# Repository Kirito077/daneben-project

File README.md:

# Daneben! — Smart Waste Bin Detection System

**Course:** Mikro-controller (5. Semester) · Hochschule Niederrhein (HSNR)  
**Antigravity Project:** `daneben-project` (`C:\Users\ekwug\.gemini\antigravity\projects\daneben-project`)  
**Workspace:** `C:\Users\ekwug\OneDrive\Documents\Deutschland\HSNR\Studium\5.Semester\Mikro-contoller\Daneben Projekt`  

---

## 📌 Project Overview
"Daneben!" is a solar-powered, retrofittable IoT Edge AI system mounted on municipal waste bins. It monitors the surrounding pavement for illegally dumped waste (bags, boxes), ignores pedestrians to preserve privacy (GDPR compliance), prompts users with acoustic messages if space remains inside the container, and reports fill/dumping status live to sanitation departments via MQTT / LoRaWAN.

---

## 📂 Repository Structure

* 📁 **`docs/`**
  * **Presentations & Pitches (1-Minute Sales Pitch & Condensed Editions):**
    * [`Daneben_Condensed_Pitch_Visual_DE_AutoNarrated_1Min.pptx`](docs/Daneben_Condensed_Pitch_Visual_DE_AutoNarrated_1Min.pptx) — **Auto-Narrated 6-Slide Pitch (Visual Edition, 54s Total)**: Fully autonomous presentation with embedded studio-quality German neural voice narration (`de-DE-KillianNeural`). When started (**F5**), it speaks the entire presentation out loud and auto-advances through all 6 slides in **exactly 54 seconds** (strictly inside 1 minute) without touching the keyboard or mouse.
    * [`Daneben_Condensed_Pitch_DE_AutoNarrated_1Min.pptx`](docs/Daneben_Condensed_Pitch_DE_AutoNarrated_1Min.pptx) — **Auto-Narrated 6-Slide Pitch (Standard Edition, 54s Total)**: Standard analytical edition with identical embedded auto-narration and 54-second automatic slide timings.
    * [`Daneben_Condensed_Pitch_Visual_DE.pptx`](docs/Daneben_Condensed_Pitch_Visual_DE.pptx) ([🇬🇧 EN Version](docs/Daneben_Condensed_Pitch_Visual_EN.pptx)) — **Condensed 6-Slide Pitch (Visual Doodle Edition)**: Streamlined 6-slide deck combining Problem 1 (side-dumping) & Problem 2 (blind fleet routes) side-by-side with vector doodles and stat callouts, omitting the CCTV/market gap slide, preserving the exploded 3D CAD production hardware architecture with native editable callouts, omitting the Geschäftsmodell, and concluding with the "Let's keep the city clean!" wrap-up slide.
    * [`Daneben_Condensed_Pitch_DE.pptx`](docs/Daneben_Condensed_Pitch_DE.pptx) ([🇬🇧 EN Version](docs/Daneben_Condensed_Pitch_EN.pptx)) — **Condensed 6-Slide Pitch (Standard Edition)**: Clean analytical 6-slide presentation with structured cards, exploded CAD hardware, municipal ROI, and closing mission slide.
    * [`Daneben_1Min_Sales_Pitch_Visual_Edition.pptx`](docs/Daneben_1Min_Sales_Pitch_Visual_Edition.pptx) ([🇩🇪 DE Version](docs/Daneben_1Min_Sales_Pitch_Visual_Edition_DE.pptx)) — **Visual Doodle Edition (Full Pitch - 9 Slides)**: Complete 9-slide pitch with animated vector illustrations, exploded 3D CAD hardware, business model, and closing slogan.
    * [`Daneben_Pitch_Visual_Edition_DE_ohne_Geschaeftsmodell.pptx`](docs/Daneben_Pitch_Visual_Edition_DE_ohne_Geschaeftsmodell.pptx) ([🇬🇧 EN Version](docs/Daneben_Pitch_Visual_Edition_EN_no_business_model.pptx)) — **Academic Edition (Ohne Hardware & Geschäftsmodell - 7 Slides)**: Streamlined 7-slide version omitting both the exploded hardware and business model slides.
    * [`Daneben_1Min_Sales_Pitch.pptx`](docs/Daneben_1Min_Sales_Pitch.pptx) ([🇩🇪 DE Version](docs/Daneben_1Min_Sales_Pitch_DE.pptx)) — **Standard Edition (Full Pitch - 9 Slides)**: Clean white 9-slide presentation with side-by-side analytical cards, labeled exploded hardware, business model, and timed speaker notes.
    * [`Daneben_Pitch_DE_ohne_Geschaeftsmodell.pptx`](docs/Daneben_Pitch_DE_ohne_Geschaeftsmodell.pptx) ([🇬🇧 EN Version](docs/Daneben_Pitch_EN_no_business_model.pptx)) — **Standard Technical Edition (Ohne Hardware & Geschäftsmodell - 7 Slides)**: 7-slide standard presentation without exploded hardware or startup business case.
    * [`Daneben_1Min_Pitch_Script_EN.pdf`](docs/Daneben_1Min_Pitch_Script_EN.pdf) ([🇩🇪 DE Version](docs/Daneben_1Min_Pitch_Script_DE.pdf)) — **Spoken Pitch Scripts**: Precise 60-second word-for-word presentation delivery script with timed stage directions (0–15s Hook, 15–30s Problem, 30–45s Solution, 45–60s CTA).
  * **Bill of Materials (BOM) — Official Production Specifications:**
    * [`Daneben_Hardware_BoM_Full.pdf`](docs/Daneben_Hardware_BoM_Full.pdf) ([📊 Excel .xlsx](docs/Daneben_Hardware_BoM_Full.xlsx)) — **Full System BOM**: Complete 13-item production specification (compute, dual sensors, audio amp, speaker, solar MPPT, Li-ion cell, Carrier Board v2 PCB, calibration & interface hardware kit, optical window, membrane vents) in clean Excel grid layout (€70.77 gross parts total).
    * [`Daneben_Hardware_BoM_Prototype.pdf`](docs/Daneben_Hardware_BoM_Prototype.pdf) ([📊 Excel .xlsx](docs/Daneben_Hardware_BoM_Prototype.xlsx)) — **Benchtop Prototype BOM**: Focused 11-item BOM containing only the core electronics and Carrier Board v2.0 electrical components (ESP32-S3 Sense, dual ultrasonic sensors, I2S amp, speaker, custom carrier PCB, 2× tactile calibration buttons, 3× status LEDs, SPDT power switch, USB-C 5V power input, screw terminals, socket headers; mechanical fasteners excluded) (€40.75 gross parts total).
    * [`Daneben_Hardware_BoM_Core.pdf`](docs/Daneben_Hardware_BoM_Core.pdf) ([📊 Excel .xlsx](docs/Daneben_Hardware_BoM_Core.xlsx)) — **Core Electronics BOM**: Focused specification for the 4 primary electronic subsystems (ESP32-S3 Sense, 2× JSN-SR04T waterproof ultrasonic, MAX98357A I2S amp, 3W speaker) with Farnell & Funduino primary vendor sourcing (€33.25 gross parts total).
    * 📁 [`docs/archive/legacy_boms/`](docs/archive/legacy_boms/) — Archived legacy HTML and duplicate BOM iterations.
  * **Visual Architecture & Mindmaps:**
    * [`Daneben_Operational_Flowchart.pdf`](docs/Daneben_Operational_Flowchart.pdf) & [`.html`](docs/Daneben_Operational_Flowchart.html) — Complete operational flowchart mapping every state to its hardware component and software functionality.
    * [`Daneben_Project_Mindmap.pdf`](docs/Daneben_Project_Mindmap.pdf) & [`.html`](docs/Daneben_Project_Mindmap.html) — Presentation-ready visual Mind Map (Landscape PDF & interactive dashboard).
    * [`Project_Mindmap.md`](docs/Project_Mindmap.md) — Raw Markdown/Mermaid Mind Map chart.
  * **Technical Reports & Blueprints:**
    * [`Enclosure_3D_Design_Report_Detailed.pdf`](docs/Enclosure_3D_Design_Report_Detailed.pdf) — 2D Orthographic Blueprint (Front, Side, Top views) with exact millimeter dimensions, waterproofing details, and exploded 3D renders.
    * [`Enclosure_3D_Design_Report.pdf`](docs/Enclosure_3D_Design_Report.pdf) — Conceptual 3D external and exploded visualizations.
  * **Engineering Documentation & Analysis:**
    * [`CONVERSATION_HISTORY.md`](docs/CONVERSATION_HISTORY.md) — Complete transcript and architectural evolution of all discussions, trade-offs (RoboDog vs. Daneben), and engineering decisions.
    * [`Project_Workflow_and_Market_Analysis.md`](docs/Project_Workflow_and_Market_Analysis.md) — Problem statement, market analysis (municipalities, smart cities, housing), SaaS revenue model, and 5-year lifespan calculation.
    * [`AI_and_System_Expansions.md`](docs/AI_and_System_Expansions.md) — Comparison between pixel-differencing and Edge AI (Edge Impulse), internal container capacity sensing, and smart fleet telemetry.
* 📁 **`hardware/`**
  * [`daneben_enclosure.scad`](hardware/daneben_enclosure.scad) — Parametric 3D CAD model for OpenSCAD.
  * [`daneben_enclosure.stl`](hardware/daneben_enclosure.stl) — Compiled 3D mesh model ready to open directly in **Autodesk Inventor** or Windows 3D Viewer.
  * [`Enclosure_and_Hardware.md`](hardware/Enclosure_and_Hardware.md) — IP67 sealing strategy, 20° sloped roof, drip edges, and isolated battery cartridge system.
  * [`Parts_List.md`](hardware/Parts_List.md) — Technical Bill of Materials (BOM) with unit costs at scale (~$29.50 BOM).
  * [`Procurement_Parts_List.md`](hardware/Procurement_Parts_List.md) — Complete purchasing list with **exact dimensions, specs, and 3 fast-shipping store links** per component (Amazon.de, BerryBase, Reichelt).
  * [`Budget_Showcase_Prototype_Template.md`](hardware/Budget_Showcase_Prototype_Template.md) — Low-cost (~€28) tabletop demonstration template for student presentations and live demo evaluations.
  * 📁 **[`Daneben_Prototype_Carrier_Board/`](hardware/Daneben_Prototype_Carrier_Board/)** — Complete KiCad 9 modular prototype carrier board project (`.kicad_pcb`, `.kicad_sch`, `.kicad_pro`, PDF/SVG exports, and generator scripts) with integrated power rails, sensor sockets, audio header, and modular expansion buses.
  * 📁 **`Daneben circuit board/`** — Original KiCad project files (`.kicad_pcb`, `.kicad_sch`, `.kicad_pro`) implementing the power management, ESP32-S3 processing, and sensor interfaces.
* 📁 **`src/`**
  * [`main.cpp`](src/main.cpp) — ESP32-S3 firmware: 2-stage distance debounce filter (8-second timer), Edge Impulse camera inference, and MQTT publishing.
  * [`internal_sensor.cpp`](src/internal_sensor.cpp) — Internal container fill level telematics (stationary upper collar angled mount, 0–100% continuous tracking with trigonometric depth correction) and MAX98357A I2S acoustic deterrent logic.
  * [`calibration.h`](src/calibration.h) — Dual tactile button calibration engine: interactive baseline zeroing, threshold configuration, EEPROM/NVS persistent storage, and status LED telemetry.

---

## ⚡ Quick Technical Specifications
* **MCU:** ESP32-S3 Sense (Dual-Core 240MHz, 8MB PSRAM, Wi-Fi / BLE, Camera interface).
* **Presence Sensor:** Multi-zone ToF (VL53L5CX) or JSN-SR04T Waterproof Ultrasonic (angled 45° at pavement).
* **Internal Sensor:** JSN-SR04T Waterproof Ultrasonic transducer mounted on the fixed upper collar/inner rim angled downward (~25°) toward the central trash cone (eliminates moving wires across swinging lids, prevents snagging during municipal emptying, and delivers continuous 0–100% capacity tracking).
* **Power:** 2&times; 18650 LiFePO4 cells (3.2V nominal, 3000mAh) + 5V 1.5W Monocrystalline solar panel + CN3791 MPPT charger.
* **Enclosure Rating:** IP67 (Polycarbonate, 20° sloped roof, drip edge, silicone O-rings, borosilicate optical glass with UV adhesive, hydrophobic ePTFE acoustic membrane for speaker).

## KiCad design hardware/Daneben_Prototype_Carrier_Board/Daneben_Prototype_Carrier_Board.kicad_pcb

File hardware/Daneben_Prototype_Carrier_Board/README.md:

# "Daneben!" — Modular Prototype Carrier Board Version 2.0 (KiCad 9)

> **Purpose:** Custom modular carrier board designed to house all electronic subsystems of the "Daneben!" system for student showcases, laboratory testing, and benchtop demonstration without messy floating wires.  
> **Course / Academic Context:** Hochschule Niederrhein (HSNR) · 5. Semester · Mikro-controller  
> **KiCad Version:** 9.0.4  
> **Dimensions:** 130.0 mm &times; 90.0 mm (FR4 2-Layer, 1.6 mm thickness, 4&times; M3 mounting holes, R=4.0 mm rounded corners)  
> **Active Production Version:** Version 2.0 (Historical V1 files archived in [`archive_v1/`](file:///c:/Users/ekwug/OneDrive/Documents/Deutschland/HSNR/Studium/5.Semester/Mikro-contoller/Daneben%20Projekt/hardware/Daneben_Prototype_Carrier_Board/archive_v1/))

---

## 1. Subsystem Architecture & Features (v2.0)

This board acts as a central modular motherboard, providing standardized sockets, mechanical standoff mounts, dedicated power conditioning, and hardware calibration controls:

```
+-----------------------------------------------------------------------------------------------------------------------+
| [H1: M3]                                                                                                     [H2: M3] |
|                                                                                                                       |
|  +---------------------------------------+      +-------------------------------+      +----------------------------+ |
|  |     AJ-SR04M DOCK 1 (OUTSIDE / FLOOR) |      |      SEEED XIAO ESP32-S3      |      |     I2S AUDIO & SPEAKER    | |
|  |                                       |      |             SENSE             |      |                            | |
|  | [Transducer Jack Exits Left <---]     |      |                               |      | [J_AMP: MAX98357A Socket]  | |
|  |                                       |      |  [J_MCU_L]         [J_MCU_R]  |      |  (2x M2.5 Standoff Holes)  | |
|  | [4x M2.5 Standoff Mounting Holes]     |      |  D0: TRIG_OUT      D7: IN_STAT|      |                            | |
|  | [J_AJ_OUT: 4-Pin Socket (5V/Trig/Echo/GND)]  |  D1: ECHO_OUT      D8: BCLK   |      | [J_SPK: 2-Pin Screw Term]  | |
|  +---------------------------------------+      |  D2: TRIG_IN       D9: LRC    |      |  (SPK+ / SPK- Differential)| |
|                                                 |  D3: ECHO_IN       D10: DIN   |      +----------------------------+ |
|                                                 |  D4: BTN_CAL_OUT   3V3: +3V3  |                                     |
|  +---------------------------------------+      |  D5: BTN_CAL_IN    GND: GND   |      +----------------------------+ |
|  |     AJ-SR04M DOCK 2 (INSIDE / DEPTH)  |      |  D6: OUT_STAT      5V: +5V    |      |     SIZABLE CALIBRATION    | |
|  |                                       |      +-------------------------------+      |     CONTROLS (12x12mm)     | |
|  | [Transducer Jack Exits Left <---]     |                                             |                            | |
|  |                                       |      +-------------------------------+      | [SW_CAL_OUT: 12x12mm Blue] | |
|  | [4x M2.5 Standoff Mounting Holes]     |      |   DEDICATED USB-C POWER ENTRY |      |  (Floor Distance Reference)| |
|  | [J_AJ_IN: 4-Pin Socket (5V/Trig/Echo/GND)]   |                               |      | [LED_CAL_OUT: Blue Status] | |
|  +---------------------------------------+      | [J_USBC: Type-C Port (5V)]    |      |                            | |
|                                                 | [R_CC1 / R_CC2: 5.1k PD]      |      | [SW_CAL_IN: 12x12mm Amber] | |
|                                                 | [SW_PWR: On/Off Slide Switch] |      |  (Bin Depth 1m-4m NVS Cal) | |
|                                                 | [C_BULK1: 100uF Bulk Reservoir]      | [LED_CAL_IN: Amber Status] | |
|                                                 | [J_EXT_5V: Screw Terminal In] |      +----------------------------+ |
|                                                 | [LED_PWR: Green Power LED]    |                                     |
|                                                 +-------------------------------+      [J_AUX: 1x6 Expansion Header]  |
| [H3: M3]                                                                                                     [H4: M3] |
+-----------------------------------------------------------------------------------------------------------------------+
```

---

## 2. Key Engineering Improvements in v2.0

### 2.1 Zero-Friction AJ-SR04M Waterproof Transducer Docks
* **Mechanical Stability:** Each AJ-SR04M sensor board is fastened to the carrier board using **4&times; M2.5 standoff screws**, eliminating wiggling, loose contacts, and vibrations.
* **Cable Clearance:** Both modules have their cylindrical metal transducer connectors positioned directly along the left PCB edge, pointing into free air. When the thick shielded transducer cables are attached, they exit outward with **zero bending friction or mechanical obstruction**.

### 2.2 Dedicated Onboard USB-C Power Entry
* Standard USB Type-C receptacle (`J_USBC`) on the bottom board edge with two 5.1 kΩ pull-down resistors (`R_CC1`, `R_CC2`) on CC1 and CC2. Automatically negotiates clean 5V (up to 3A) from modern USB-PD power banks and phone chargers.
* Onboard slide switch (`SW_PWR`) and green power LED (`LED_PWR`).
* 100 µF bulk capacitor (`C_BULK1`) buffers the sudden current draws of the MAX98357A Class-D amplifier.

### 2.3 Sizable 12&times;12 mm Dual Calibration Pushbuttons
* Whisbins and municipal waste bins vary widely in geometry (standard 120L/240L bins are ~1.0m deep, whereas large commercial or underground containers can be 2.0m to 4.0m deep).
* **`SW_CAL_OUT` (Outside / Floor Reference):** Runs 15 ultrasonic pings, averages baseline floor distance, and persists it into non-volatile storage (`Preferences` / NVS).
* **`SW_CAL_IN` (Inside / Bin Depth Reference):** One-click empty-bin calibration that auto-scales full percentage (0–100%) dynamically for any container depth.
* Driven by [`src/calibration.h`](file:///c:/Users/ekwug/OneDrive/Documents/Deutschland/HSNR/Studium/5.Semester/Mikro-contoller/Daneben%20Projekt/src/calibration.h).

---

## 3. How to View in KiCad 3D Viewer

1. Open [`Daneben_Prototype_Carrier_Board.kicad_pro`](file:///c:/Users/ekwug/OneDrive/Documents/Deutschland/HSNR/Studium/5.Semester/Mikro-contoller/Daneben%20Projekt/hardware/Daneben_Prototype_Carrier_Board/Daneben_Prototype_Carrier_Board.kicad_pro) in KiCad.
2. Open the PCB Editor (`Daneben_Prototype_Carrier_Board.kicad_pcb`).
3. Press **`Alt + 3`** (or go to **View &rarr; 3D Viewer**).
4. Real-time 3D models will display with exact millimeter alignment for the AJ-SR04M modules, Seeed XIAO Sense, MAX98357A, USB-C jack, and 12x12mm switches.

---

## 4. File Manifest

### Active Production Files (Version 2.0):
* [`Daneben_Prototype_Carrier_Board.kicad_pro`](file:///c:/Users/ekwug/OneDrive/Documents/Deutschland/HSNR/Studium/5.Semester/Mikro-contoller/Daneben%20Projekt/hardware/Daneben_Prototype_Carrier_Board/Daneben_Prototype_Carrier_Board.kicad_pro): Main project.
* [`Daneben_Prototype_Carrier_Board.kicad_sch`](file:///c:/Users/ekwug/OneDrive/Documents/Deutschland/HSNR/Studium/5.Semester/Mikro-contoller/Daneben%20Projekt/hardware/Daneben_Prototype_Carrier_Board/Daneben_Prototype_Carrier_Board.kicad_sch): Full master schematic.
* [`Daneben_Prototype_Carrier_Board.kicad_pcb`](file:///c:/Users/ekwug/OneDrive/Documents/Deutschland/HSNR/Studium/5.Semester/Mikro-contoller/Daneben%20Projekt/hardware/Daneben_Prototype_Carrier_Board/Daneben_Prototype_Carrier_Board.kicad_pcb): Complete routed 130x90mm PCB.
* [`carrier_board_schematic.pdf`](file:///c:/Users/ekwug/OneDrive/Documents/Deutschland/HSNR/Studium/5.Semester/Mikro-contoller/Daneben%20Projekt/hardware/Daneben_Prototype_Carrier_Board/carrier_board_schematic.pdf): Master schematic PDF.
* [`carrier_board_pcb_layout.pdf`](file:///c:/Users/ekwug/OneDrive/Documents/Deutschland/HSNR/Studium/5.Semester/Mikro-contoller/Daneben%20Projekt/hardware/Daneben_Prototype_Carrier_Board/carrier_board_pcb_layout.pdf): PCB fabrication layout PDF.
* [`carrier_board_v2_3d_isometric.png`](file:///c:/Users/ekwug/OneDrive/Documents/Deutschland/HSNR/Studium/5.Semester/Mikro-contoller/Daneben%20Projekt/hardware/Daneben_Prototype_Carrier_Board/carrier_board_v2_3d_isometric.png): High-res 3D isometric render.
* [`carrier_board_v2_3d_top.png`](file:///c:/Users/ekwug/OneDrive/Documents/Deutschland/HSNR/Studium/5.Semester/Mikro-contoller/Daneben%20Projekt/hardware/Daneben_Prototype_Carrier_Board/carrier_board_v2_3d_top.png): High-res 3D top-down render.
* [`carrier_board_v2_3d_front_angle.png`](file:///c:/Users/ekwug/OneDrive/Documents/Deutschland/HSNR/Studium/5.Semester/Mikro-contoller/Daneben%20Projekt/hardware/Daneben_Prototype_Carrier_Board/carrier_board_v2_3d_front_angle.png): High-res 3D front-angle render.
* [`build_v2_pcb.py`](file:///c:/Users/ekwug/OneDrive/Documents/Deutschland/HSNR/Studium/5.Semester/Mikro-contoller/Daneben%20Projekt/hardware/Daneben_Prototype_Carrier_Board/build_v2_pcb.py): Automated board generator.
* [`build_v2_schematic.py`](file:///c:/Users/ekwug/OneDrive/Documents/Deutschland/HSNR/Studium/5.Semester/Mikro-contoller/Daneben%20Projekt/hardware/Daneben_Prototype_Carrier_Board/build_v2_schematic.py): Automated schematic generator.
* [`generate_v2_3d_models.py`](file:///c:/Users/ekwug/OneDrive/Documents/Deutschland/HSNR/Studium/5.Semester/Mikro-contoller/Daneben%20Projekt/hardware/Daneben_Prototype_Carrier_Board/generate_v2_3d_models.py): Automated VRML 3D models generator.

### Archived Files:
* [`archive_v1/`](file:///c:/Users/ekwug/OneDrive/Documents/Deutschland/HSNR/Studium/5.Semester/Mikro-contoller/Daneben%20Projekt/hardware/Daneben_Prototype_Carrier_Board/archive_v1/): Contains all legacy Carrier Board Version 1.0 files and test scripts.

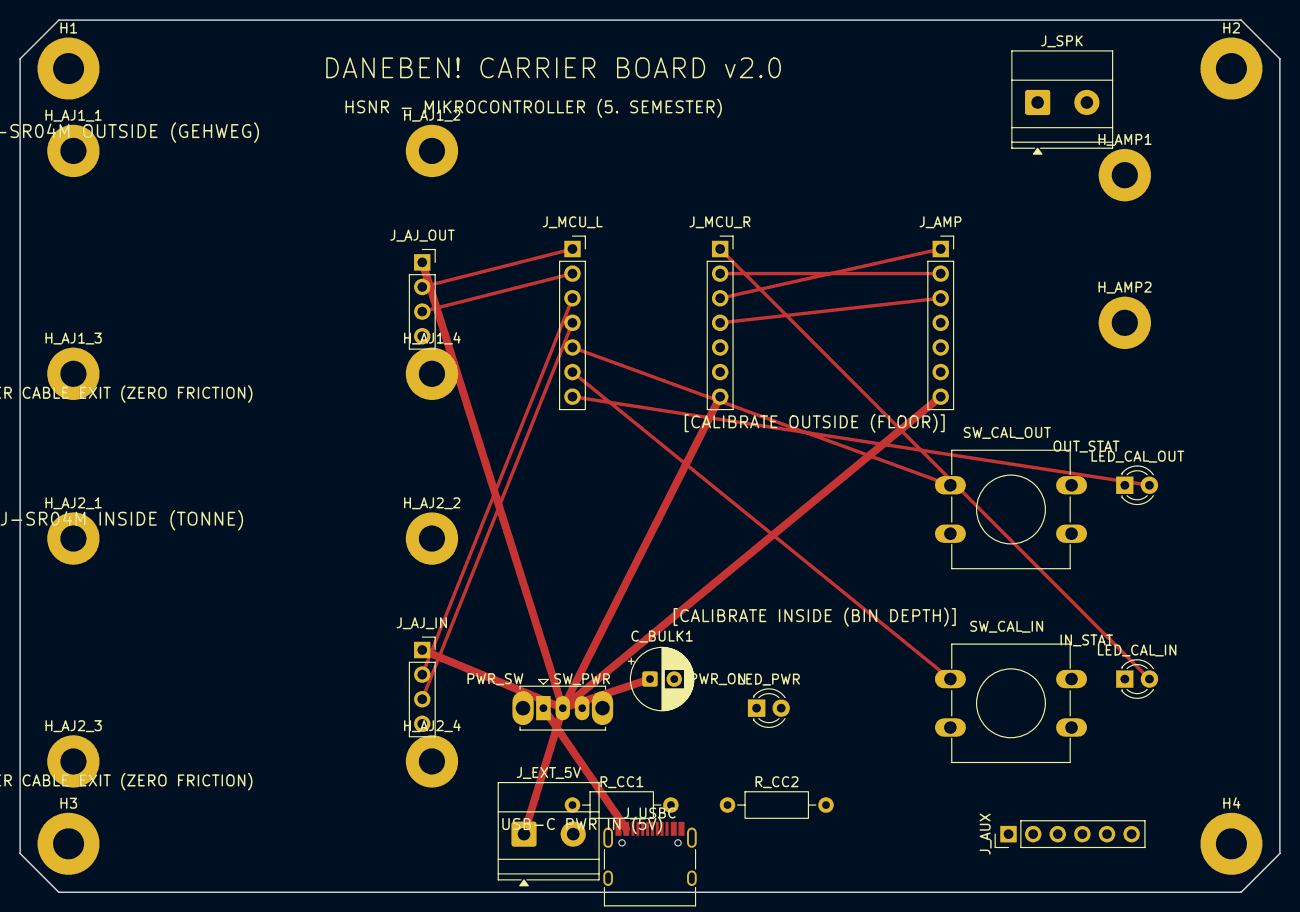
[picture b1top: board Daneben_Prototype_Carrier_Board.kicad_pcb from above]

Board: 2 copper layers, 130.0 x 90.0 mm, 32 parts (0 on the bottom side), 17 nets.

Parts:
C_BULK1: 100uF; CP_Radial_D6.3mm_P2.50mm
H1, H2, H3, H4: M3_HOLE; MountingHole_3.2mm_M3_Pad
H_AJ1_1, H_AJ1_2, H_AJ1_3, H_AJ1_4, H_AJ2_1, H_AJ2_2, H_AJ2_3, H_AJ2_4: M2.5_STANDOFF; MountingHole_2.7mm_M2.5_Pad
H_AMP1, H_AMP2: M2.5_STANDOFF; MountingHole_2.7mm_M2.5_Pad
J_AJ_IN: AJ_SR04M_IN; PinSocket_1x04_P2.54mm_Vertical
J_AJ_OUT: AJ_SR04M_OUT; PinSocket_1x04_P2.54mm_Vertical
J_AMP: MAX98357A; PinSocket_1x07_P2.54mm_Vertical
J_AUX: AUX_EXPANSION; PinHeader_1x06_P2.54mm_Vertical
J_EXT_5V: ALT_5V_IN; TerminalBlock_Phoenix_MKDS-1,5-2-5.08_1x02_P5.08mm_Horizont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
J_MCU_L: XIAO_L; PinSocket_1x07_P2.54mm_Vertical
J_MCU_R: XIAO_R; PinSocket_1x07_P2.54mm_Vertical
J_SPK: SPEAKER_OUT; TerminalBlock_Phoenix_MKDS-1,5-2-5.08_1x02_P5.08mm_Horizont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
J_USBC: USB_C_PWR; USB_C_Receptacle_HRO_TYPE-C-31-M-12
LED_CAL_IN: AMBER_IN_STAT; LED_D3.0mm
LED_CAL_OUT: BLUE_OUT_STAT; LED_D3.0mm
LED_PWR: GREEN_PWR; LED_D3.0mm
R_CC1, R_CC2: 5.1k; R_Axial_DIN0207_L6.3mm_D2.5mm_P10.16mm_Horizontal
SW_CAL_IN: CAL_INSIDE; SW_PUSH-12mm
SW_CAL_OUT: CAL_OUTSIDE; SW_PUSH-12mm
SW_PWR: PWR_SWITCH; SW_Slide_SPDT_Straight_CK_OS102011MS2Q

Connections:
+3V3: J_AUX.1, J_MCU_R.5
+5V: C_BULK1.1, J_AJ_IN.1, J_AJ_OUT.1, J_AMP.7, J_EXT_5V.1, J_MCU_R.7, LED_PWR.2, SW_PWR.2
BTN_CAL_IN: J_AUX.5, J_MCU_L.6, SW_CAL_IN.1
BTN_CAL_OUT: J_AUX.4, J_MCU_L.5, SW_CAL_OUT.1
CC1: J_USBC.A5, R_CC1.1
CC2: J_USBC.B5, R_CC2.1
ECHO_IN: J_AJ_IN.3, J_MCU_L.4
ECHO_OUT: J_AJ_OUT.3, J_MCU_L.2
GND: C_BULK1.2, J_AJ_IN.4, J_AJ_OUT.4, J_AMP.4, J_AMP.5, J_AMP.6, J_AUX.6, J_EXT_5V.2, J_MCU_R.6, J_USBC.A1, J_USBC.A12, J_USBC.B1, J_USBC.B12, J_USBC.S1, LED_CAL_IN.1, LED_CAL_OUT.1, LED_PWR.1, R_CC1.2, R_CC2.2, SW_CAL_IN.2, SW_CAL_OUT.2
I2S_BCLK: J_AMP.2, J_MCU_R.2
I2S_DIN: J_AMP.3, J_MCU_R.4
I2S_LRC: J_AMP.1, J_MCU_R.3
LED_CAL_IN: J_AUX.3, J_MCU_R.1, LED_CAL_IN.2
LED_CAL_OUT: J_AUX.2, J_MCU_L.7, LED_CAL_OUT.2
TRIG_IN: J_AJ_IN.2, J_MCU_L.3
TRIG_OUT: J_AJ_OUT.2, J_MCU_L.1
VBUS_RAW: J_USBC.A4, J_USBC.A9, J_USBC.B4, J_USBC.B9, SW_PWR.1, SW_PWR.3

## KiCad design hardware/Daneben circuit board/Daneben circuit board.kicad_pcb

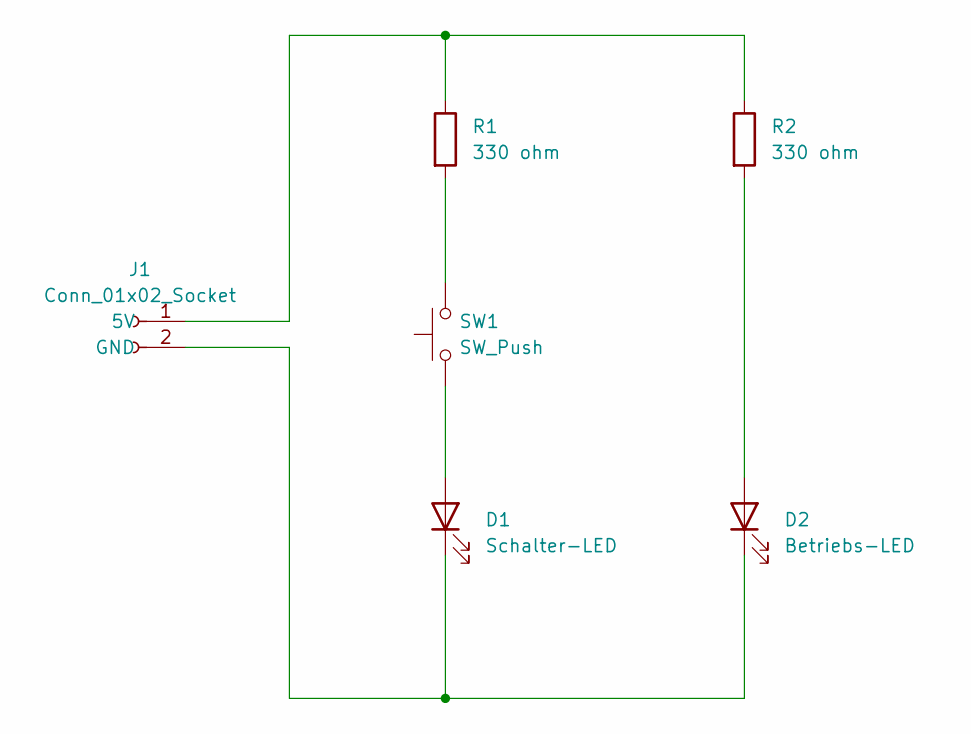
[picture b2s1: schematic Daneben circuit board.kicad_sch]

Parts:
D1: Schalter-LED; LED_D5.0mm
D2: Betriebs-LED; LED_D5.0mm
J1: Conn_01x02_Socket; PinSocket_1x02_P2.54mm_Vertical
R1, R2: 330 ohm; R_Axial_DIN0207_L6.3mm_D2.5mm_P10.16mm_Horizontal
SW1: SW_Push; SW_PUSH_6mm

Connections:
unnamed: D1.2 (A), SW1.1
unnamed: D1.1 (K), D2.1 (K), J1.2 (GND)
unnamed: D2.2 (A), R2.2
unnamed: J1.1 (5V), R1.1, R2.1
unnamed: R1.2, SW1.2

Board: 2 copper layers, 6 parts (0 on the bottom side), 5 nets, no tracks yet.

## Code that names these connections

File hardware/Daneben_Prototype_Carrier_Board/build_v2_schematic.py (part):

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    sch += add_text("1. DEDICATED USB-C POWER ENTRY & DISTRIBUTION", 30, 42, 2.2)
    # USB-C Connector (Conn_01x06)
    sch += add_sym("Connector_Generic:Conn_01x06", "J_USBC", "USB_C_PWR_5V", "Connector_USB:USB_C_Receptacle_HRO_TYPE-C-31-M-12", 45, 60)
    sch += add_label("VBUS_RAW", 35, 60 - 6.35, 180)
    sch += add_label("CC1", 35, 60 - 3.81, 180)
    sch += add_label("CC2", 35, 60 - 1.27, 180)
    sch += add_label("NC", 35, 60 + 1.27, 180)
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
    # Power Switch
    sch += add_sym("Connector_Generic:Conn_01x02", "SW_PWR", "PWR_SWITCH", "Button_Switch_THT:SW_Slide_SPDT_Straight_CK_OS102011MS2Q", 90, 60)
    sch += add_label("VBUS_RAW", 80, 58.73, 180)
    sch += add_label("+5V", 80, 61.27, 180)

    # Power Indicator LED
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    # Outside Sensor Dock (Pavement / Floor)
    sch += add_sym("Connector_Generic:Conn_01x04", "J_AJ_OUT", "AJ-SR04M_OUTSIDE_DOCK", "Connector_PinSocket_2.54mm:PinSocket_1x04_P2.54mm_Vertical", 50, 150)
    sch += add_label("+5V", 40, 150 - 3.81, 180)
    sch += add_label("TRIG_OUT", 40, 150 - 1.27, 180)
    sch += add_label("ECHO_OUT", 40, 150 + 1.27, 180)
    sch += add_label("GND", 40, 150 + 3.81, 180)

    # Inside Sensor Dock (Bin Depth / Fill Level)
    sch += add_sym("Connector_Generic:Conn_01x04", "J_AJ_IN", "AJ-SR04M_INSIDE_DOCK", "Connector_PinSocket_2.54mm:PinSocket_1x04_P2.54mm_Vertical", 100, 150)
    sch += add_label("+5V", 90, 150 - 3.81, 180)
    sch += add_label("TRIG_IN", 90, 150 - 1.27, 180)
    sch += add_label("ECHO_IN", 90, 150 + 1.27, 180)
    sch += add_label("GND", 90, 150 + 3.81, 180)

    # 4. SIZABLE DUAL CALIBRATION BUTTONS & STATUS LEDS
    sch += add_text("4. SIZABLE 12x12mm CALIBRATION CONTROLS (OUTSIDE & INSIDE)", 150, 130, 2.2)
    # Outside Calibration Button (SW_CAL_OUT)
    sch += add_sym("Switch:SW_Push", "SW_CAL_OUT", "CAL_OUTSIDE_12x12", "Button_Switch_THT:SW_PUSH-12mm", 170, 150)
    sch += add_label("BTN_CAL_OUT", 160, 150, 180)
    sch += add_wire(160, 150, 164.92, 150)
    sch += add_label("GND", 180, 150, 0)
    sch += add_wire(175.08, 150, 180, 150)

    # Outside Calibration Status LED
    sch += add_sym("Device:R", "R_LED_OUT", "1k", "Resistor_THT:R_Axial_DIN0207_L6.3mm_D2.5mm_P10.16mm_Horizontal", 205, 150, 90)
    sch += add_label("LED_CAL_OUT", 195, 150, 180)
    sch += add_wire(195, 150, 201.19, 150)
    sch += add_sym("Device:LED", "LED_CAL_OUT", "BLUE_OUT_STAT", "LED_THT:LED_D3.0mm", 220, 150, 90)
    sch += add_wire(208.81, 150, 216.19, 150)
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
    # Inside Calibration Button (SW_CAL_IN)
    sch += add_sym("Switch:SW_Push", "SW_CAL_IN", "CAL_INSIDE_12x12", "Button_Switch_THT:SW_PUSH-12mm", 170, 175)
    sch += add_label("BTN_CAL_IN", 160, 175, 180)
    sch += add_wire(160, 175, 164.92, 175)
    sch += add_label("GND", 180, 175, 0)
    sch += add_wire(175.08, 175, 180, 175)

    # Inside Calibration Status LED
    sch += add_sym("Device:R", "R_LED_IN", "1k", "Resistor_THT:R_Axial_DIN0207_L6.3mm_D2.5mm_P10.16mm_Horizontal", 205, 175, 90)
    sch += add_label("LED_CAL_IN", 195, 175, 180)
    sch += add_wire(195, 175, 201.19, 175)
    sch += add_sym("Device:LED", "LED_CAL_IN", "AMBER_IN_STAT", "LED_THT:LED_D3.0mm", 220, 175, 90)
    sch += add_wire(208.81, 175, 216.19, 175)
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
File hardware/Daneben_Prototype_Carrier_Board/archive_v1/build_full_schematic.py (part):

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    # Section 3: Seeed Studio XIAO ESP32-S3 Sense Carrier (Center)
    sch += add_text("2. SEEED STUDIO XIAO ESP32-S3 SENSE CARRIER", 150, 45, 2.2)
    sch += add_sym("Connector_Generic:Conn_01x07", "J_MCU_L", "XIAO_LEFT_PINS", "Connector_PinSocket_2.54mm:PinSocket_1x07_P2.54mm_Vertical", 170, 75)
    mcu_l_nets = ["AUX_GPIO", "BTN_TEST", "TRIG_EXT", "ECHO_EXT", "I2S_BCLK", "I2S_LRC", "I2S_DIN"]
    for i, dy in enumerate([7.62, 5.08, 2.54, 0, -2.54, -5.08, -7.62]):
        sch += add_label(mcu_l_nets[i], 160, 75 - dy, 180)

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    # Section 6: Modular Expansion Bus & Diagnostics
    sch += add_text("5. EXPANSION BUS & TEST SIMULATION", 260, 130, 2.2)
    sch += add_sym("Connector_Generic:Conn_01x08", "J_EXP", "EXPANSION_BUS", "Connector_PinHeader_2.54mm:PinHeader_1x08_P2.54mm_Vertical", 280, 155)
    exp_nets = ["+5V", "+3V3", "GND", "I2S_BCLK", "I2S_LRC", "I2S_DIN", "STATUS_LED", "AUX_GPIO"]
    for i, dy in enumerate([8.89, 6.35, 3.81, 1.27, -1.27, -3.81, -6.35, -8.89]):
        sch += add_label(exp_nets[i], 270, 155 - dy, 180)

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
